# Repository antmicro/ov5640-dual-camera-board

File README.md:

# Antmicro's OV5640 Dual Camera Board

Copyright (c) 2017-2024 [Antmicro](https://www.antmicro.com)

## Overview

This project contains open hardware design files for a camera board supporting two [OV5640](https://cdn.sparkfun.com/datasheets/Sensors/LightImaging/OV5640_datasheet.pdf) image sensors from OmniVision. 
These RGB sensors provide a rolling shutter and offer a resolution of 5MP (2591x1944).
The design files for this project are provided and maintained in KiCad.

### Project structure

The main directory contains the KiCad design files, LICENSE and README.
The remaining files are stored in the following directories:

* ``img`` - contains graphics for this README
* ``doc`` - contains generated schematics and other documentation
* ``lib`` - contains KiCad component library

## Key features

* Two OV5640 image sensors placed on a PCB
* Fastening holes spaced by 20mm for a standard S-mount lens holder
* Each sensor is accessible through an independent 2-lane MIPI CSI-2 interface
* Separate I2C buses for sensor configuration 
* Unified, 50-pin FFC interface
* On-board clock generator for driving the image sensors 

The OV5640 Dual Camera board is electrically compatible with a variety of processing platforms created by Antmicro.
Below is a list of a few selected ones:

* [Jetson Nano Baseboard](https://github.com/antmicro/jetson-nano-baseboard) supporting NVIDIA [Jetson Nano](https://developer.nvidia.com/embedded/jetson-nano), Jetson [TX2 NX](https://developer.nvidia.com/embedded/jetson-tx2-nx), Jetson [Xavier NX](https://www.nvidia.com/en-us/autonomous-machines/embedded-systems/jetson-xavier-nx/) System on Modules
* [Jetson Orin Baseboard](https://github.com/antmicro/jetson-orin-baseboard) supporting NVIDIA Jetson Orin NX, Jetson Orin Nano
* [Kria K26 Devboard](https://github.com/antmicro/kria-k26-devboard) supporting AMD-Xilinx [KRIA K26](https://www.xilinx.com/products/som/kria/k26c-commercial.html) System on Module
* [Google Coral Baseboard](https://github.com/antmicro/google-coral-baseboard) supporting [Google Coral](https://coral.ai/products/som) System on Module
* [Snapdragon 845 Baseboard](https://github.com/antmicro/snapdragon-845-baseboard) based on Quectel SA800 SoM with Qualcomm [Snapdragon 845 Mobile Platform](https://www.qualcomm.com/products/mobile/snapdragon/smartphones/snapdragon-8-series-mobile-platforms/snapdragon-845-mobile-platform)
* [Snapdragon 625 Baseboard](https://github.com/antmicro/snapdragon-625-baseboard) based on Quectel SC606T SoM with Qualcomm [Snapdragon 625 Mobile Platform](https://www.qualcomm.com/products/mobile/snapdragon/smartphones/snapdragon-6-series-mobile-platforms/snapdragon-625-mobile-platform)

## License

This project is licensed under the [Apache-2.0](LICENSE) license.

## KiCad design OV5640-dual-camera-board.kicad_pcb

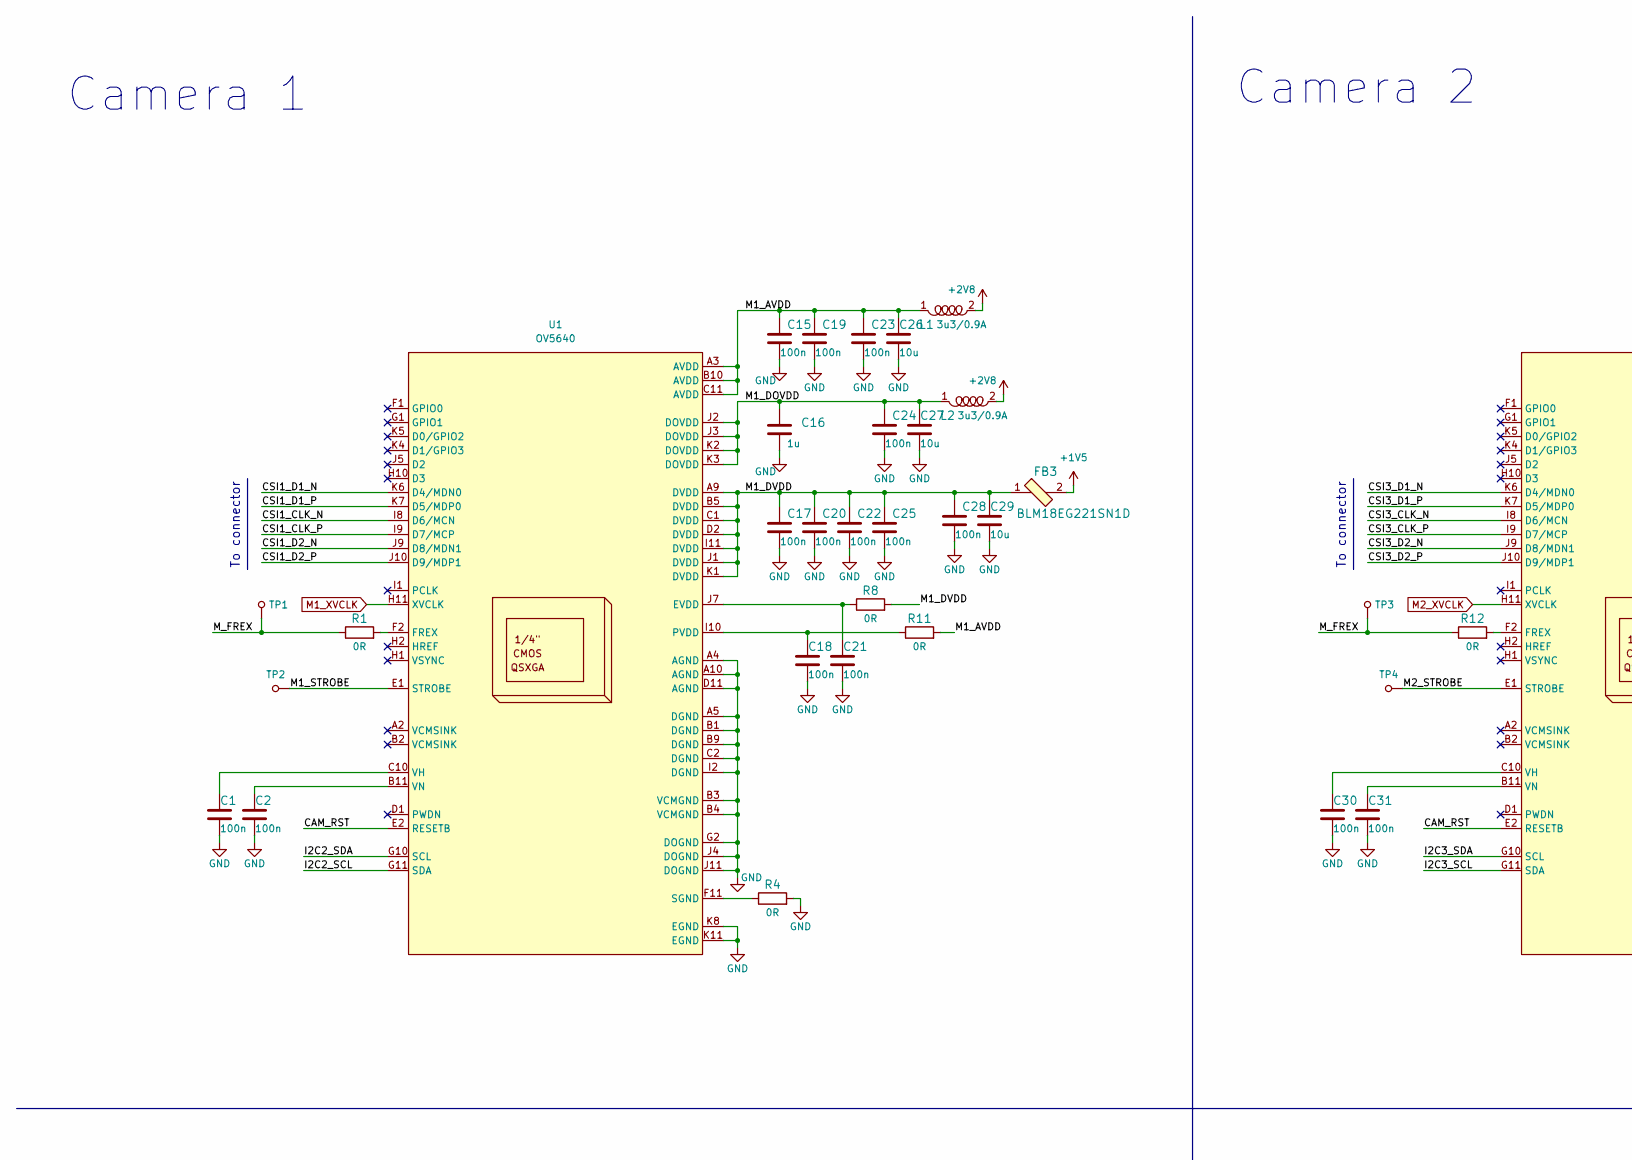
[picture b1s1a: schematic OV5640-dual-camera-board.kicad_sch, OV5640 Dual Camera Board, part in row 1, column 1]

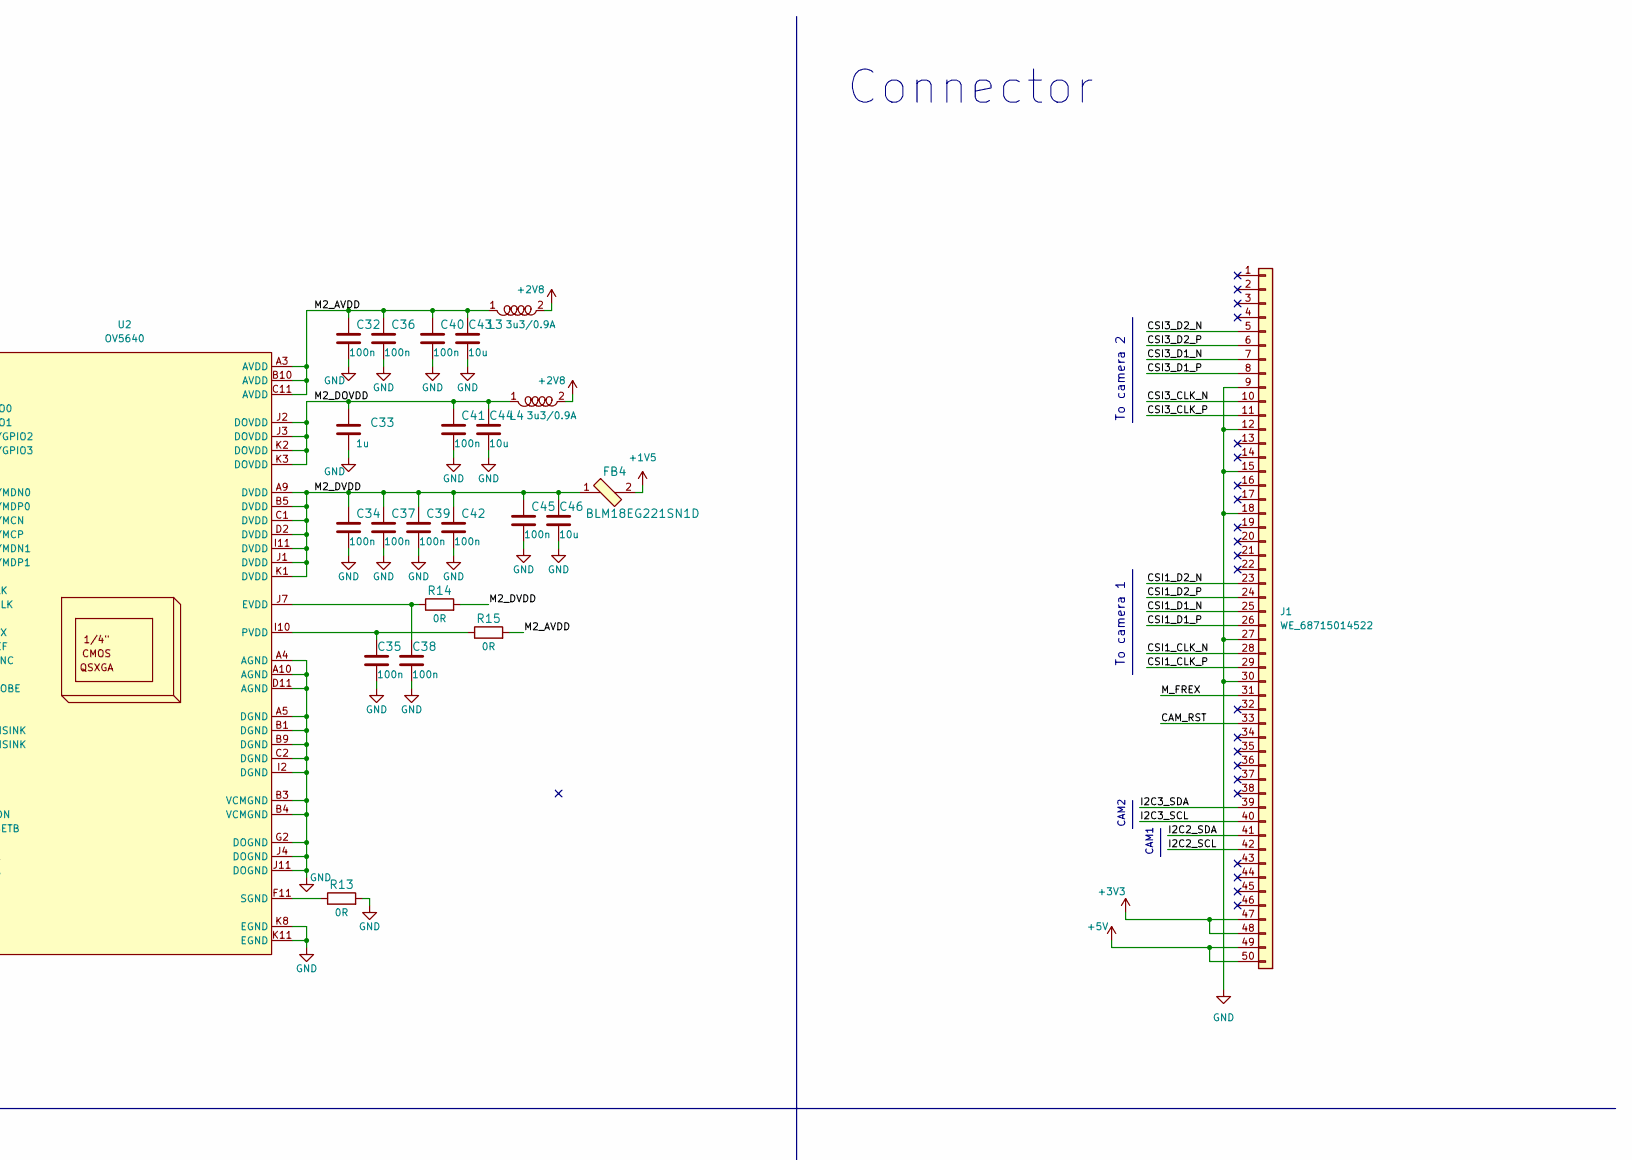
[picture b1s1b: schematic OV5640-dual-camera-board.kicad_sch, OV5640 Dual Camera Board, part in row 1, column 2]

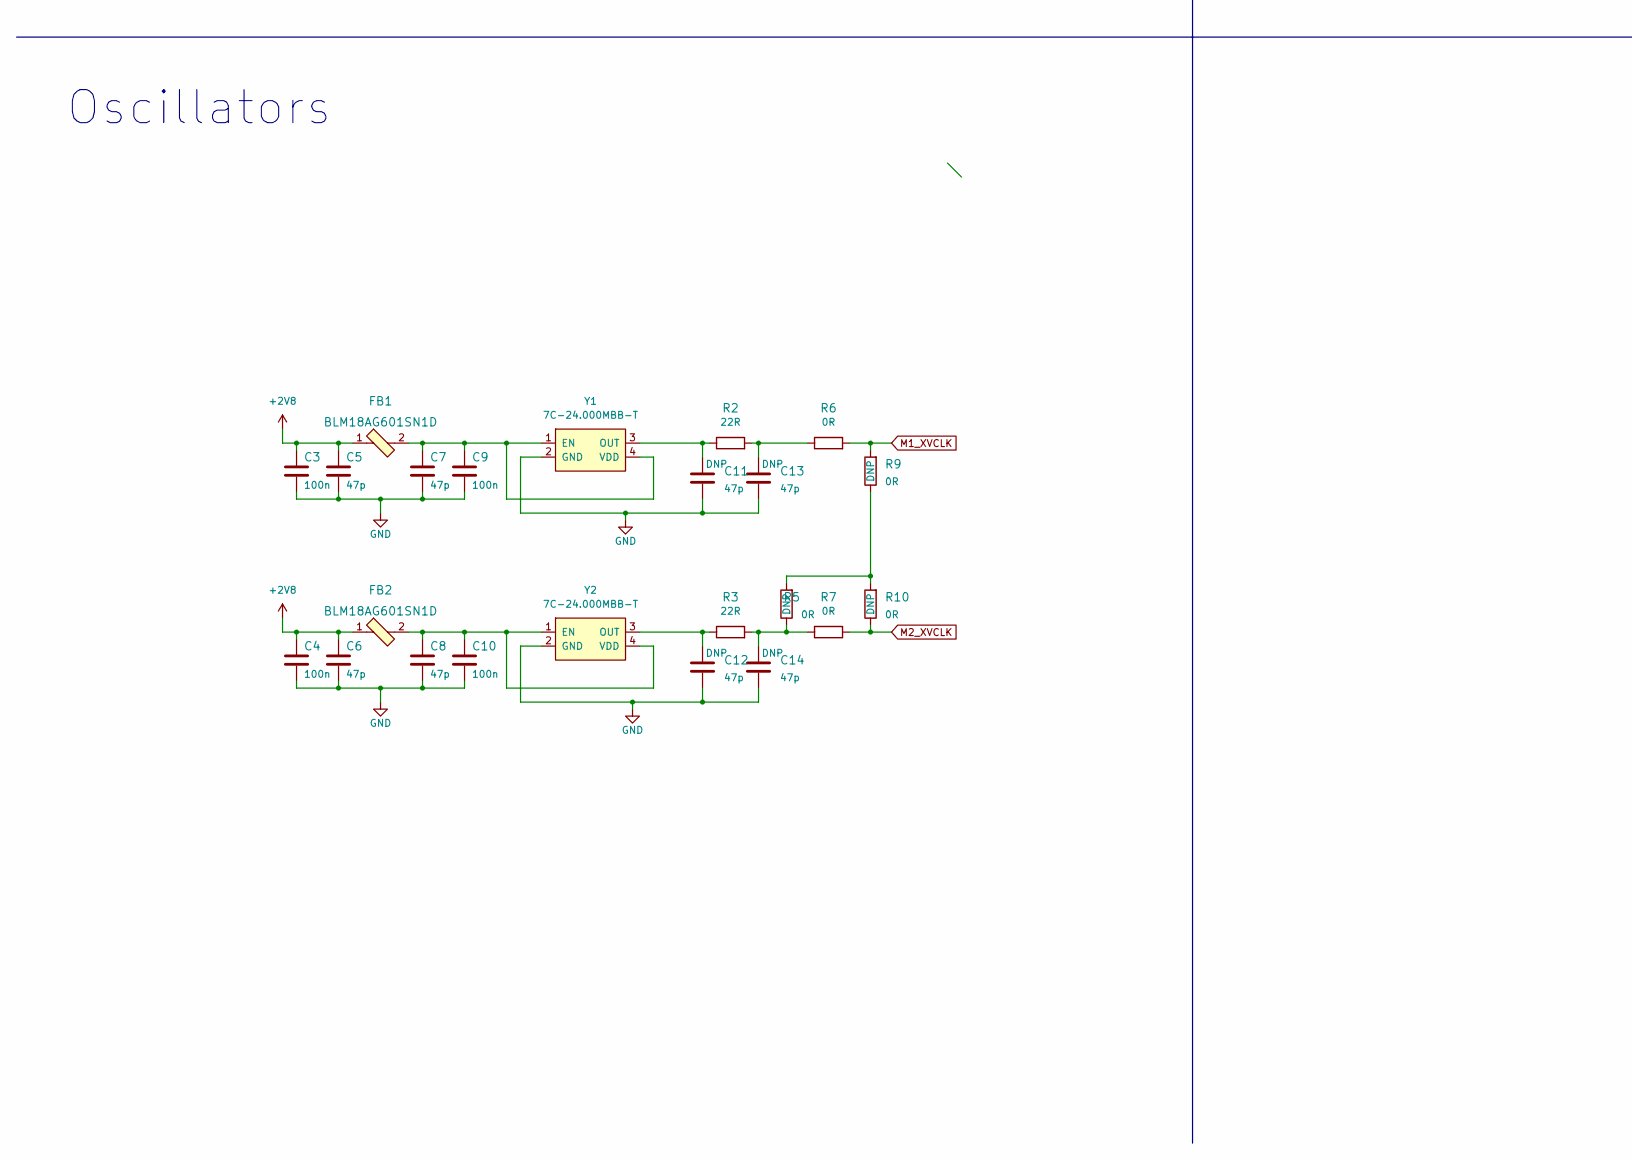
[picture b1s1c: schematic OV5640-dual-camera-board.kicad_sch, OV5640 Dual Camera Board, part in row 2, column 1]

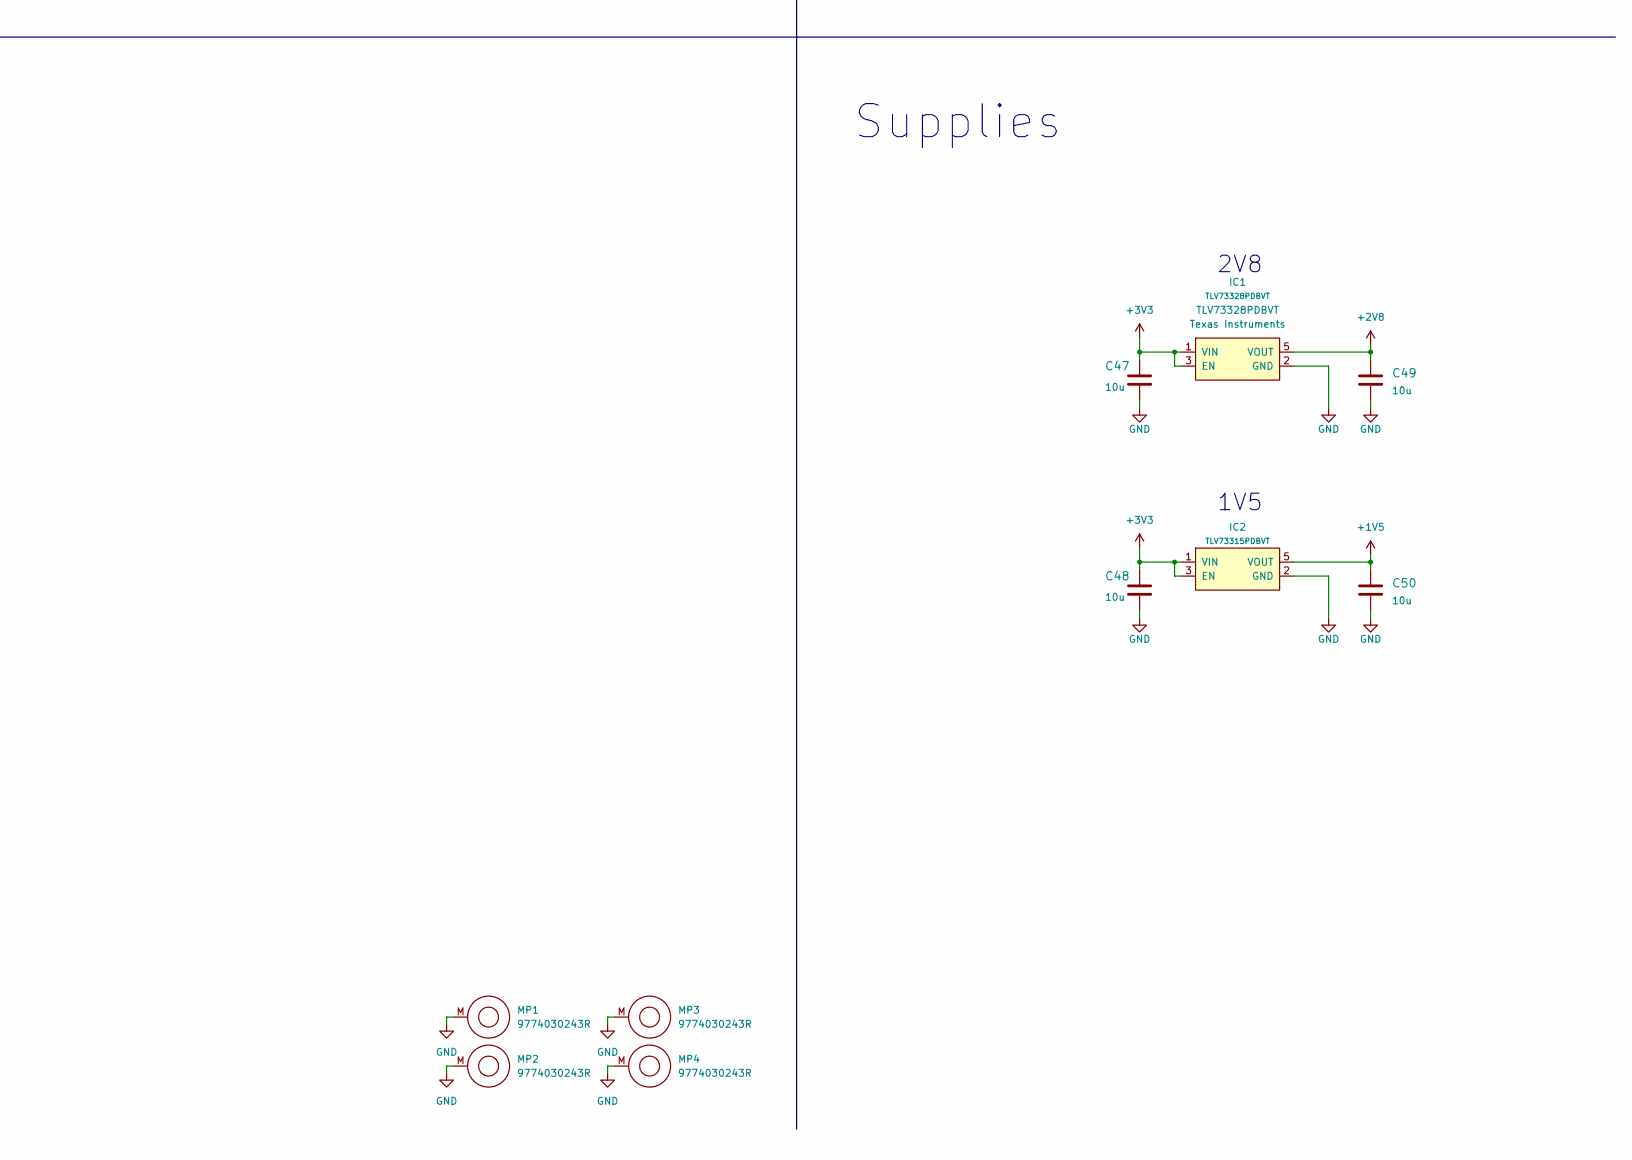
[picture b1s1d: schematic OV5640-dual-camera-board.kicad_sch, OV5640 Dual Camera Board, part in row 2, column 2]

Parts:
C1, C2, C3, C4, C9, C10, C15, C17, C18, C19, C20, C21, C22, C23, C24, C25, C28, C30, C31, C32, C34, C35, C36, C37, C38, C39, C40, C41, C42, C45: C_100n_0402; 0402-cap; MPN GRM155R61H104KE14D
C5, C6, C7, C8, C11, C12, C13, C14: C_47p_0402; 0402-cap; MPN C0402C470J5GACTU
C16, C33: C_1u_0402; 0402-cap; MPN C1005X6S1A105K050BC
C26, C27, C29, C43, C44, C46, C47, C48, C49, C50: C_10u_0603; 0603-cap; MPN GRM188R61A106KE69D
FB1, FB2: BLM18AG601SN1D; 0603; MPN BLM18AG601SN1D
FB3, FB4: BLM18EG221SN1D; 0603; MPN BLM18EG221SN1D
IC1: TLV73328PDBVT; SOT-23-5; MPN TLV73328PDBVT
IC2: TLV73315PDBVT; SOT-23-5; MPN TLV73312PDBVT
J1: WE_68715014522; MPN 68715014522
L1, L2, L3, L4: MLP2012S3R3MT; 0805-res; MPN MLP2012S3R3MT
MP1, MP2, MP3, MP4: 9774030243R; MPN 9774030243R
R1, R4, R5, R6, R7, R8, R9, R10, R11, R12, R13, R14, R15: R_0R_0402; 0402-res; MPN ERJ2GE0R00X
R2, R3: R_22R_0402; 0402-res; MPN CRCW040222R0FKED
TP1, TP2, TP3, TP4: TP_SMD1MM; Testpoint_smd_1mm
U1, U2: OV5640; MPN OV5640
Y1, Y2: 7C-24.000MBB-T; MPN 7C-24.000MBB-T

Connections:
+1V5: C50.1, FB3.2, FB4.2, IC2.5 (VOUT)
+2V8: C3.1, C4.1, C5.1, C6.1, C49.1, FB1.1, FB2.1, IC1.5 (VOUT), L1.2, L2.2, L3.2, L4.2
+3V3: C47.1, C48.1, IC1.1 (VIN), IC1.3 (EN), IC2.1 (VIN), IC2.3 (EN), J1.47, J1.48
+5V: J1.49, J1.50
/CAM_RST: J1.33, U1.E2 (RESETB), U2.E2 (RESETB)
/CSI1_CLK_N: J1.28, U1.I8 (D6/MCN)
/CSI1_CLK_P: J1.29, U1.I9 (D7/MCP)
/CSI1_D1_N: J1.25, U1.K6 (D4/MDN0)
/CSI1_D1_P: J1.26, U1.K7 (D5/MDP0)
/CSI1_D2_N: J1.23, U1.J9 (D8/MDN1)
/CSI1_D2_P: J1.24, U1.J10 (D9/MDP1)
/CSI3_CLK_N: J1.10, U2.I8 (D6/MCN)
/CSI3_CLK_P: J1.11, U2.I9 (D7/MCP)
/CSI3_D1_N: J1.7, U2.K6 (D4/MDN0)
/CSI3_D1_P: J1.8, U2.K7 (D5/MDP0)
/CSI3_D2_N: J1.5, U2.J9 (D8/MDN1)
/CSI3_D2_P: J1.6, U2.J10 (D9/MDP1)
/I2C2_SCL: J1.42, U1.G11 (SDA)
/I2C2_SDA: J1.41, U1.G10 (SCL)
/I2C3_SCL: J1.40, U2.G11 (SDA)
/I2C3_SDA: J1.39, U2.G10 (SCL)
/M1_AVDD: C15.1, C19.1, C23.1, C26.1, L1.1, R11.2, U1.A3 (AVDD), U1.B10 (AVDD), U1.C11 (AVDD)
/M1_DOVDD: C16.1, C24.1, C27.1, L2.1, U1.J2 (DOVDD), U1.J3 (DOVDD), U1.K2 (DOVDD), U1.K3 (DOVDD)
/M1_DVDD: C17.1, C20.1, C22.1, C25.1, C28.1, C29.1, FB3.1, R8.2, U1.A9 (DVDD), U1.B5 (DVDD), U1.C1 (DVDD), U1.D2 (DVDD), U1.I11 (DVDD), U1.J1 (DVDD), U1.K1 (DVDD)
/M1_STROBE: TP2.1, U1.E1 (STROBE)
/M2_AVDD: C32.1, C36.1, C40.1, C43.1, L3.1, R15.2, U2.A3 (AVDD), U2.B10 (AVDD), U2.C11 (AVDD)
/M2_DOVDD: C33.1, C41.1, C44.1, L4.1, U2.J2 (DOVDD), U2.J3 (DOVDD), U2.K2 (DOVDD), U2.K3 (DOVDD)
/M2_DVDD: C34.1, C37.1, C39.1, C42.1, C45.1, C46.1, FB4.1, R14.2, U2.A9 (DVDD), U2.B5 (DVDD), U2.C1 (DVDD), U2.D2 (DVDD), U2.I11 (DVDD), U2.J1 (DVDD), U2.K1 (DVDD)
/M2_STROBE: TP4.1, U2.E1 (STROBE)
/M_FREX: J1.31, R1.1, R12.1, TP1.1, TP3.1
GND: C1.2, C2.2, C3.2, C4.2, C5.2, C6.2, C7.2, C8.2, C9.2, C10.2, C11.2, C12.2, C13.2, C14.2, C15.2, C16.2, C17.2, C18.2, C19.2, C20.2, C21.2, C22.2, C23.2, C24.2, C25.2, C26.2, C27.2, C28.2, C29.2, C30.2, C31.2, C32.2, C33.2, C34.2, C35.2, C36.2, C37.2, C38.2, C39.2, C40.2, C41.2, C42.2, C43.2, C44.2, C45.2, C46.2, C47.2, C48.2, C49.2, C50.2, IC1.2 (GND), IC2.2 (GND), J1.9, J1.12, J1.15, J1.18, J1.27, J1.30, MP1.M, MP2.M, MP3.M, MP4.M, R4.2, R13.2, U1.A4 (AGND), U1.A5 (DGND), U1.A10 (AGND), U1.B1 (DGND), U1.B3 (VCMGND), U1.B4 (VCMGND), U1.B9 (DGND), U1.C2 (DGND), U1.D11 (AGND), U1.G2 (DOGND), U1.I2 (DGND), U1.J4 (DOGND), U1.J11 (DOGND), U1.K8 (EGND), U1.K11 (EGND), U2.A4 (AGND), U2.A5 (DGND), U2.A10 (AGND), U2.B1 (DGND), U2.B3 (VCMGND), U2.B4 (VCMGND), U2.B9 (DGND), U2.C2 (DGND), U2.D11 (AGND), U2.G2 (DOGND), U2.I2 (DGND), U2.J4 (DOGND), U2.J11 (DOGND), U2.K8 (EGND), U2.K11 (EGND), Y1.2 (GND), Y2.2 (GND)
M1_XVCLK: R6.2, R9.2, U1.H11 (XVCLK)
M2_XVCLK: R7.1, R10.1, U2.H11 (XVCLK)
unnamed: C1.1, U1.C10 (VH)
unnamed: C2.1, U1.B11 (VN)
unnamed: C7.1, C9.1, FB1.2, Y1.1 (EN), Y1.4 (VDD)
unnamed: C8.1, C10.1, FB2.2, Y2.1 (EN), Y2.4 (VDD)
unnamed: C11.1, R2.1, Y1.3 (OUT)
unnamed: C12.1, R3.1, Y2.3 (OUT)
unnamed: C13.1, R2.2, R6.1
unnamed: C14.1, R3.2, R5.1, R7.2
unnamed: C18.1, R11.1, U1.I10 (PVDD)
unnamed: C21.1, R8.1, U1.J7 (EVDD)
unnamed: C30.1, U2.C10 (VH)
unnamed: C31.1, U2.B11 (VN)
unnamed: C35.1, R15.1, U2.I10 (PVDD)
unnamed: C38.1, R14.1, U2.J7 (EVDD)
unnamed: R1.2, U1.F2 (FREX)
unnamed: R4.1, U1.F11 (SGND)
unnamed: R5.2, R9.1, R10.2
unnamed: R12.2, U2.F2 (FREX)
unnamed: R13.1, U2.F11 (SGND)

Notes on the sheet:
Camera 1
To connector
Supplies
To camera 1
Connector
1V5
CAM1
Oscillators
2V8
CAM2
Camera 2
To camera 2

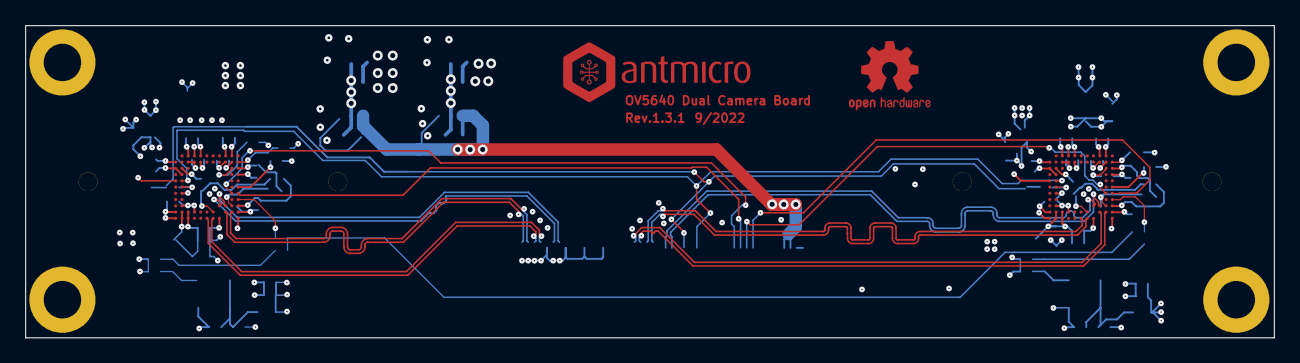
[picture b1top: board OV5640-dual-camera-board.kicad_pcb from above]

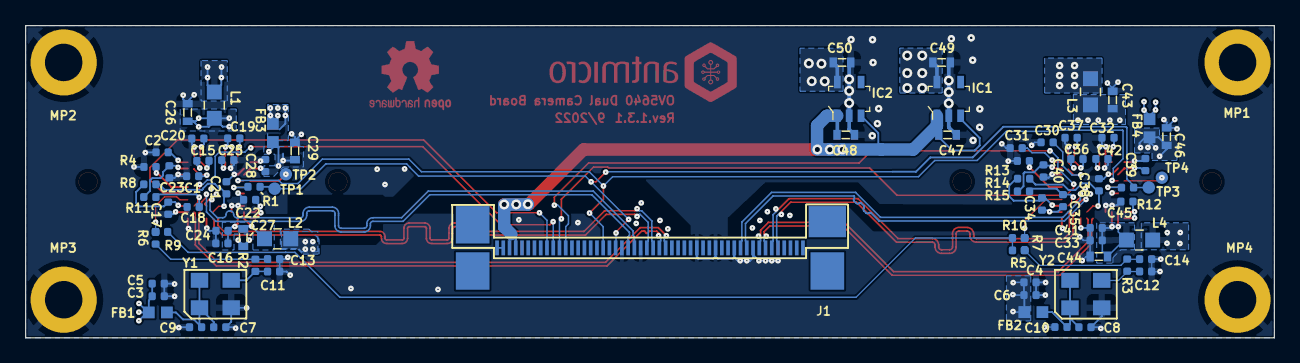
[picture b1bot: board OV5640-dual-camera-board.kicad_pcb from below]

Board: 4 copper layers, 100.0 x 25.0 mm, 88 parts (86 on the bottom side), 52 nets.

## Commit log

2023-04-25 Add initial KiCad desgin files
2023-04-25 Add LICENSE
2023-04-25 Add initial README
2023-04-25 README: replace photo, add more links to the platforms
2023-04-25 Notes added by 'git notes add'
2024-12-18 Add OHP assets

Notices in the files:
parts and their libraries:
License: MIT
